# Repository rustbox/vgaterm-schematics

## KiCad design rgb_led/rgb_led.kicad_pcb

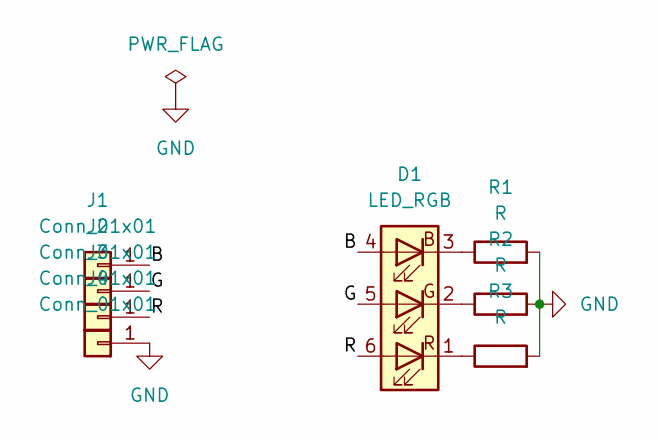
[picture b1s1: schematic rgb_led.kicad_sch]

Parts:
D1: LED_RGB; LED_Avago_PLCC6_3x2.8mm
J1, J2, J3, J4: Conn_01x01; SolderWire-0.1sqmm_1x01_D0.4mm_OD1mm_Relief
R1, R2, R3: R; R_0805_2012Metric_Pad1.20x1.40mm_HandSolder

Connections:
/B: D1.4 (BA), J1.1
/G: D1.5 (GA), J2.1
/R: D1.6 (RA), J3.1
GND: J4.1, R1.2, R2.2, R3.2
unnamed: D1.3 (BK), R1.1
unnamed: D1.2 (GK), R2.1
unnamed: D1.1 (RK), R3.1

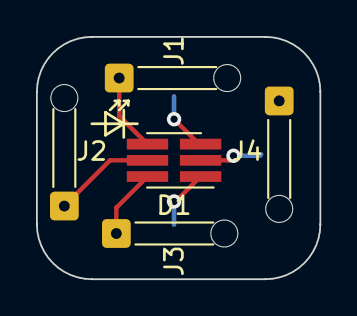
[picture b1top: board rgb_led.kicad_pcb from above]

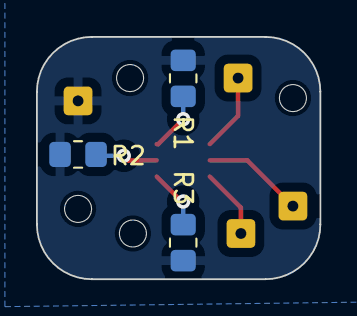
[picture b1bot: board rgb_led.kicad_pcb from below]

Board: 2 copper layers, 15.7 x 13.5 mm, 8 parts (3 on the bottom side), 7 nets.
